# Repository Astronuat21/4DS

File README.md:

Hallo! Welcome to the Github Repository for the 4DS.

4DS is a solo project by Astronuat21 (me!!) aiming to make a dual screen console _akin to the Nintendo DS's_ but with stronger hardware, better battery life and specs in general. The device is also much larger than the ones you might have at home; coming in at around 19x11.5x3cm, the device is better suited for people with bigger hands who may find uncomfortability using even the stardard XL models. The hardware mostly tops the Switch, using the Lattepanda Mu SoC and it's N100 CPU, alongside 16GB of RAM and expandable Gen 3 SSD storage. If you so choose, this project should also be compatible with the upgraded N305 version (although it will be almost useless due to its higher PSU requirements). **NOTE: THIS WILL NOT WORK WITH THE LATTEPANDA MU ULTRA**

This repository contains all the PCB files used in this project, including schematics and circuit boards. **Assuming everything works,** you should be able to reproduce the exact boards I used and reprint them for yourself. Also included are all the 3D files used in 3D printing or other purposes as well as some *outdated -_-* images to look at. They can be found in **/3D Models** and **/Images** respectively. You will also need some of the additional programs included for things like the RP2354 Microcontroller, alongside some other helpful scripts, which can be found in **/Programs**.

I built this to challenge myself to make a console that I would be proud to daily drive. My 2DS XL is great, but it definitely can't play my Steam library, and while I _can_ fit a Switch in some pockets, it dosen't quite have the extensive game library (for what I actually play). Unlike the _New (or not really)_ DS, which can play NES, SNES, GB/GBA, DS, and 3DS games as well as N64 and Gamecube to some extent. The Switch needs Nintendo Online for that as far as I know, and I HATE SUBSCRIPTIONS (Also its not even all the games). So thats where I've ended up now, with the great opportunity to flex superior intellect on some friends.

I may to make a sort of v2 version of this, there are quite a few fundemental issues with the design that cant really be fixed without starting over completely. I wouldn't really bother with that unless I find a way to make huge changes, like an insane side reduction, or adding a dGPU. I would probably make that a seperate repository, but it dosen't matter for now since I have other project ideas I want to do next.

If you intend to use this repository for any reason, **PLEASE CREDIT ME!!** I am happy to have others use this project as a reference or recreate what I have built, you can contact me with whatever you make, I would be honored. In the future, a _full-ish_ guide will be provided so that you can build your own 4DS if you'd like, but hopefully the repository is clear enough that you can do it on your own.

**DISCLAIMER:** The 4DS and all its files is under the AGPL-3.0 license. I'm therefore technically allowing this repository to used for things like commercial purposes, but trust me, you really don't want to start using this repo just all on your own like that. My warning to you is that _many decisions made here were done from extensive research and considerations from dozens of specifications and datasheets, some areas of this design are much more sensitive than expected, and some areas are not._ I am happy to clarify certain things, but depending on what you hope to use this for, I may not give my time to help you if I do not support it. Dont expect me to help you out if your goal is to throw it with some AI Slop. I'm giving this warning not because you must consult me, but if you choose not to... **Find someone to wish you good luck. You're going to need it.**

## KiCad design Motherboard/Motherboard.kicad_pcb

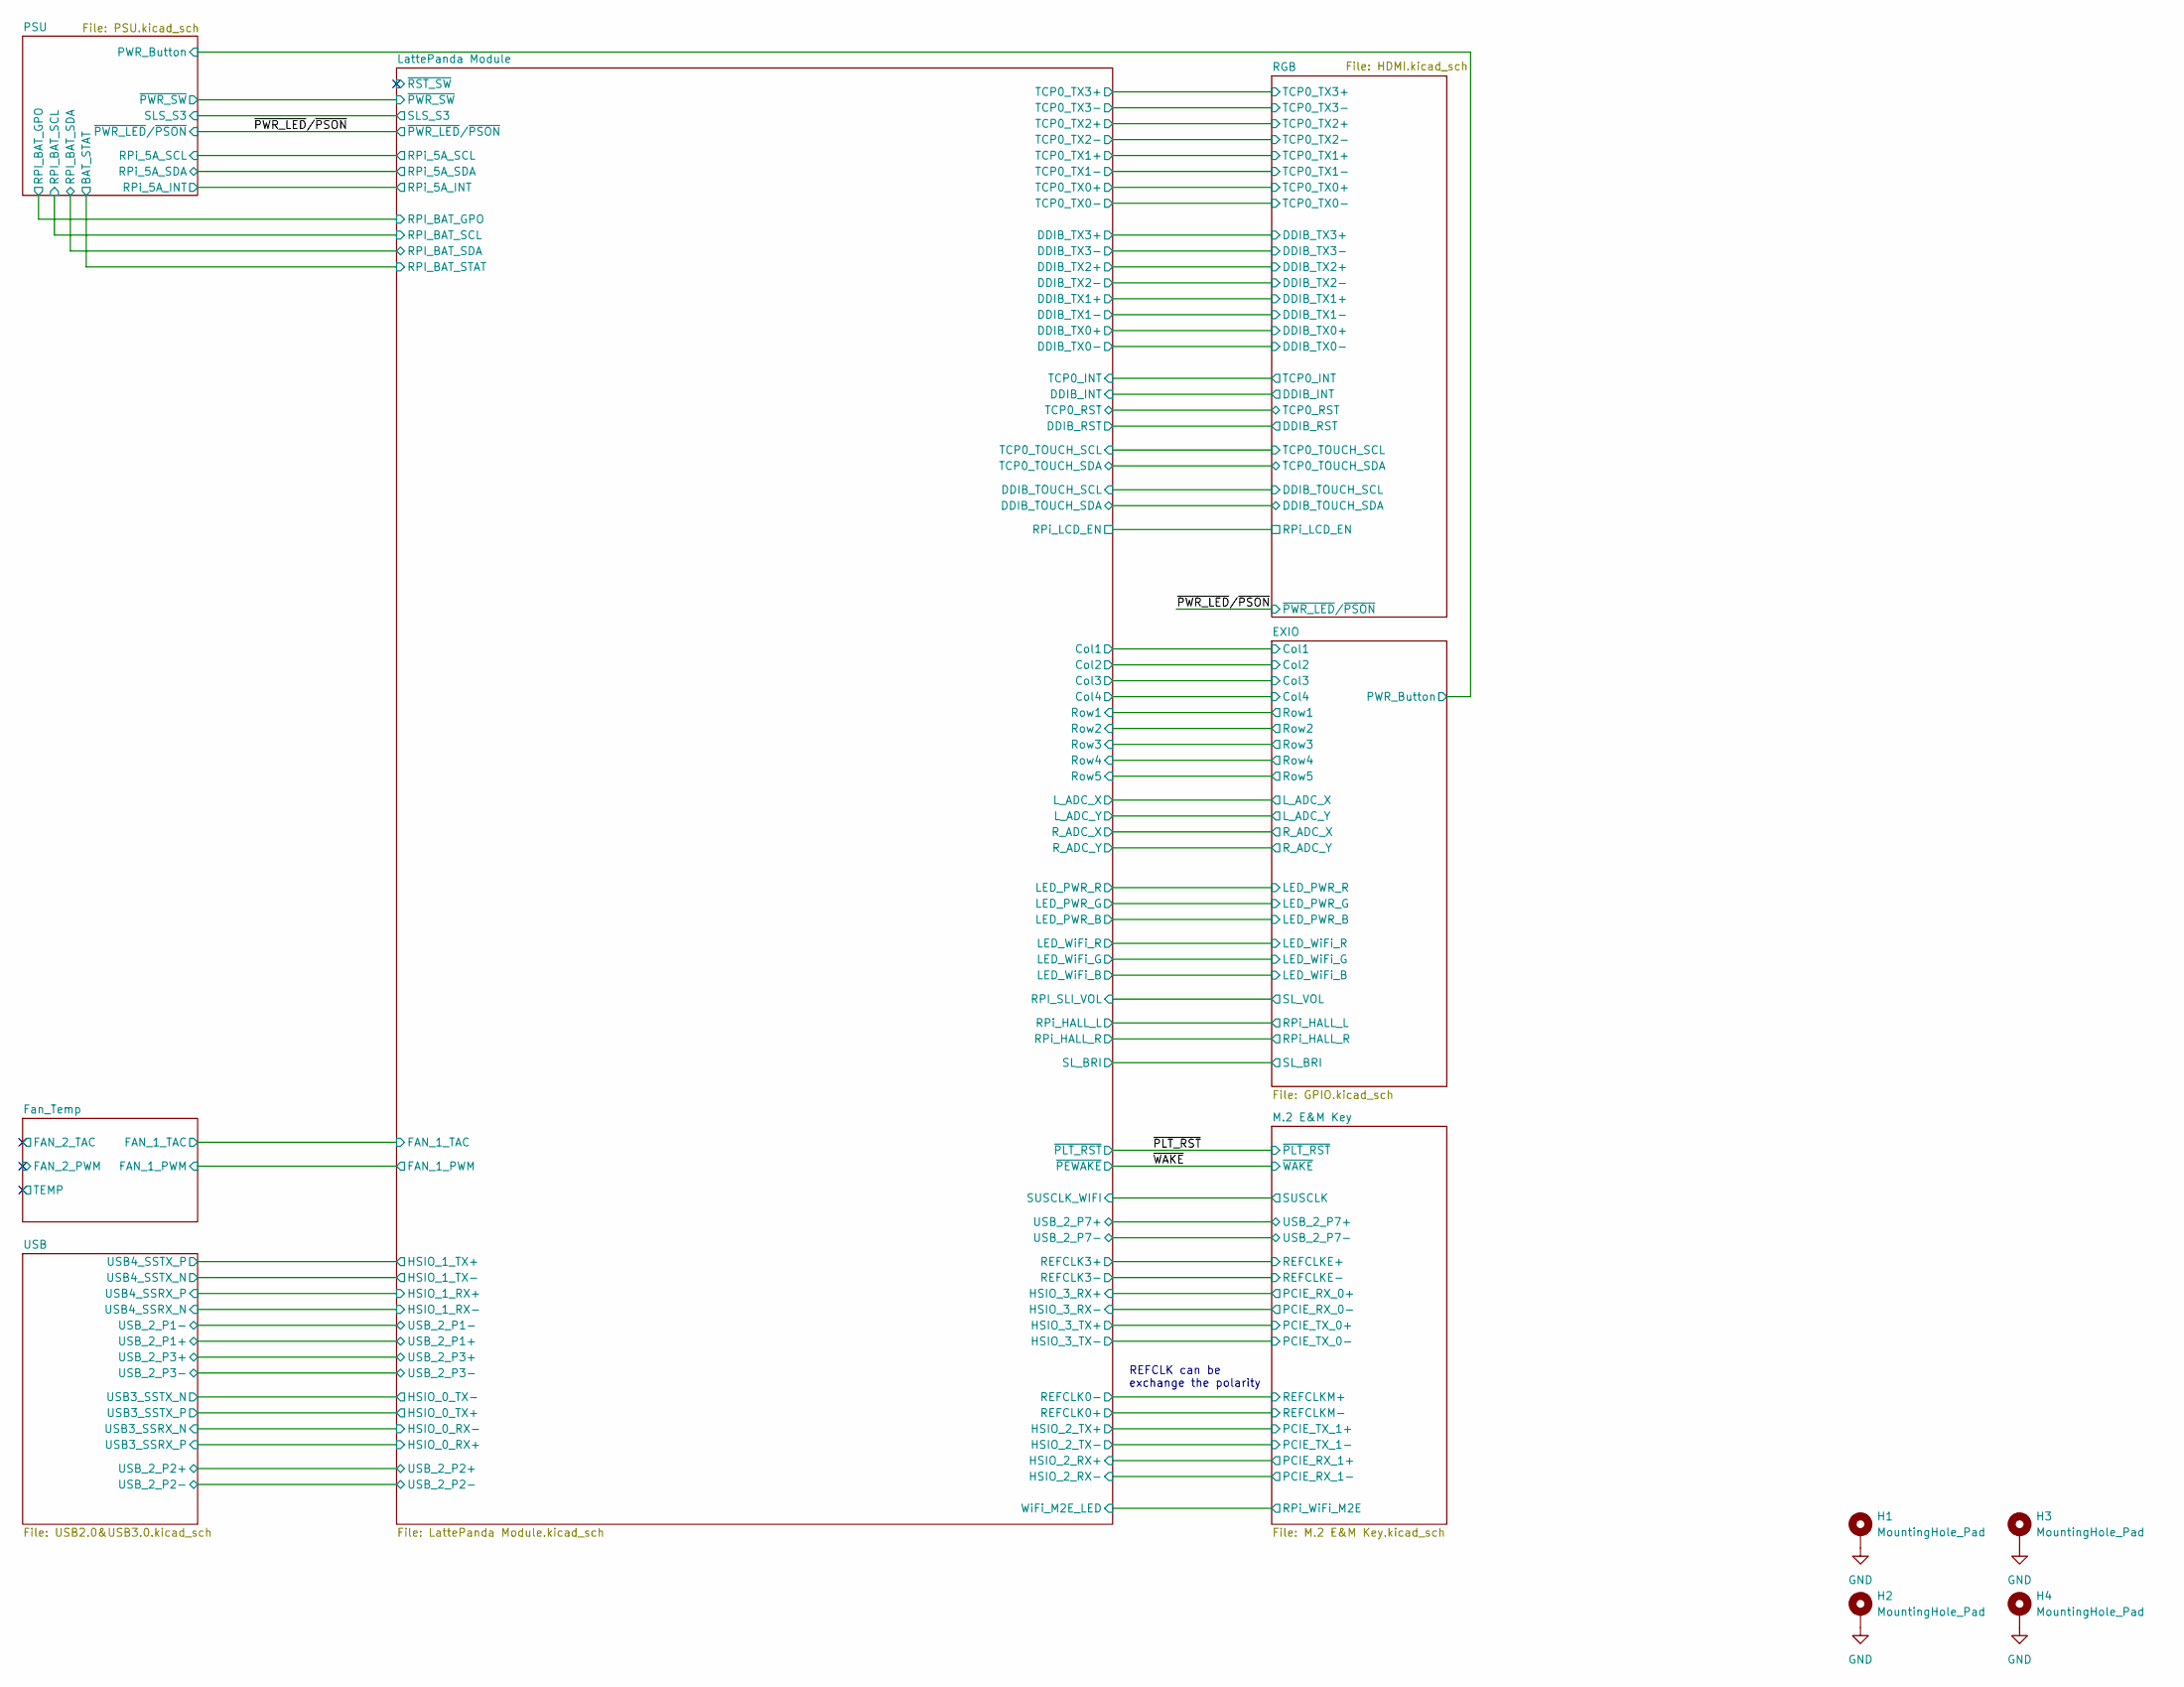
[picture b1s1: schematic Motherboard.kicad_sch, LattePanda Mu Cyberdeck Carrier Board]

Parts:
H1, H2, H3, H4: MountingHole_Pad; MountingHole_3.2mm_M3_Pad_Via

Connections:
GND: H1.1 (1_1), H2.1 (1_1), H3.1 (1_1), H4.1 (1_1); also elsewhere on the board

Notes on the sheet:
REFCLK can be exchange the polarity
